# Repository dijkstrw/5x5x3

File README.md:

5x5x3
-----

My third take on a 5x5 macro keyboard, built on top of ZMK / Zephyr. The board
is a custom 5x5 matrix carried by a nice!nano v2 module, with a rotary encoder
on the side and a 25-LED SK6803 strip behind the keys.

What this repo adds on top of stock ZMK lives in `zmk-config/` and is loaded as
an out-of-tree Zephyr module:

- **Per-key light groups**. Each of the 25 LEDs is assigned to a group
  (`DESKTOP`, `VOLUME`, `HID`, `BATTERY`, `LAYER`, `ENDPOINT`, `PROFILE`) via
  the `zmk,light-group` and `zmk,behavior-led-layout` bindings. The group's
  current value indexes into a per-group HSV palette (`zmk,color-group` +
  `zmk,behavior-hsv`), so the LED grid reflects keyboard state at a glance:
  desktop number, volume level, output endpoint, BLE profile, layer, caps/num
  lock, battery, etc.
- **Color effects**. `src/color-effect.c` implements smooth HSV transitions
  for state changes, so values fade rather than snap.
- **`lightgroup` shell command**. A Zephyr shell over USB CDC ACM
  exposing `lightgroup battery|desktop|endpoint|hid|
  layer|profile|volume <value>` allows the host to drive the LED state
  directly. This is needed to update `desktop` and can be used to
  debug the other states.
- **Custom board**. `boards/dijkstra/5x5x3` defines the
  nice!nano-based matrix, the rotary encoder node, and the SK6803 SPI
  LED strip.

Schematic
---------

A kicad schematic and layout for 2 boards lives in `schematic`. The
bottom board carries the nice!nano v2, battery, on/off switch,
blackmagic/arm swd programming port, and breaks out to connections for
the top board. The top board is carries Kailh v2 low profile switches,
sk6803 leds underneath each switch.

Default keymap
--------------

The shipping keymap (`zmk-config/boards/dijkstra/5x5x3/5x5x3.keymap`) is a
small worked example of every custom trait above. Excerpt:

    keymap {
        compatible = "zmk,keymap";
        default_layer {
            bindings = <
                &kp F13       &kp F14       &kp F15       &kp F16       &kp K_MUTE
                &kp F17       &kp F18       &kp F19       &kp F20       &kp F21
                &kp RC(LEFT)  &kp LEFT      &kp K_PP      &kp RIGHT     &kp RC(RIGHT)
                &kp K_APP     &kp C_AL_DOCS &kp C_AL_LOCK &kp C_AL_FILES&kp C_AL_WWW
                &out OUT_TOG  &bt BT_NXT    &kp F22       &kp F23       &kp F24
            >;
            sensor-bindings = <&inc_dec_kp C_VOL_UP C_VOL_DN>;
        };
    };

The bottom-left two keys exercise BLE: `&out OUT_TOG` toggles between USB
and BLE output, `&bt BT_NXT` cycles BLE profile slots. The encoder is wired
through `sensor-bindings` to send `C_VOL_UP` / `C_VOL_DN`.

`ledlayout` maps the physical LED order on the SK6803 strip to the row/col
grid (the strip snakes, so row 1 reverses):

    ledlayout {
        compatible = "zmk,behavior-led-layout";
        bindings = [ 00 01 02 03 04
                     09 08 07 06 05
                     0a 0b 0c 0d 0e
                     13 12 11 10 0f
                     14 15 16 17 18 ];
    };

`lightgroup` assigns each LED to a state-driven group. Here rows 1-2 show the
active desktop, row 3 the volume bar, row 4 caps/num lock + battery, row 5
endpoint / BLE profile / active layer:

    lightgroup {
        compatible = "zmk,light-group";
        default_layer {
            bindings = [ LG_DESKTOP  LG_DESKTOP  LG_DESKTOP  LG_DESKTOP  LG_DESKTOP
                         LG_DESKTOP  LG_DESKTOP  LG_DESKTOP  LG_DESKTOP  LG_DESKTOP
                         LG_VOLUME   LG_VOLUME   LG_VOLUME   LG_VOLUME   LG_VOLUME
                         LG_HID      LG_HID      LG_HID      LG_BATTERY  LG_BATTERY
                         LG_ENDPOINT LG_PROFILE  LG_LAYER    LG_LAYER    LG_LAYER  ];
        };
    };

`colorgroup` provides the HSV palette each group indexes into. For example
battery has five colors representing the 0/25/50/75/100% buckets, desktops
have ten colors for ten desktops, endpoints have three (USB + two BLE):

    colorgroup {
        compatible = "zmk,color-group";
        batterys  { colors = <&hsv HSV_MAGENTA &hsv HSV_RED &hsv HSV_YELLOW &hsv HSV_GREEN &hsv HSV_GREEN>; };
        desktops  { colors = <&hsv HSV_CHARTREUSE &hsv HSV_YELLOW &hsv HSV_ROSE &hsv HSV_VIOLET &hsv HSV_AZURE
                              &hsv HSV_MAGENTA &hsv HSV_VOLTA &hsv HSV_CYAN &hsv HSV_SPRING &hsv HSV_CRIMSON>; };
        endpoints { colors = <&hsv HSV_RED &hsv HSV_GREEN &hsv HSV_BLUE>; };
        ...
    };

Together: ZMK events (layer change, BLE profile change, battery level,
HID caps/num indicator, serial cli update) update each group's value,
the group's current value picks a color from the palette, and the LEDs
assigned to that group on the active layer fade to it.

Building
--------

5x5x3 assumes you have `direnv` and that `.envrc` is automatically
sourced. This will setup a local `.venv` and install `west` using
`uv`.

After that you need `zmk` for keyboard source firmware files, `zephyr`
for the rtos source, which includes an usb and bt stack, and the NRF52
hal, and finally an SDK for cross-compiling to NRF52.

``` shell
make init
```

Retrieves the `zmk` and `zephyr` source, and installs all python
modules we need for building.

If you have not developed with `zephyr` before you also need a Zephyr
SDK. Go to the `zmk` directory and run `west sdk install`.

Note that your source directory will balloon to between 1.5 and almost
5GB due to all the downloaded dependencies.

With all deps loaded;

``` shell
make build
```

Will build a lean production firmware that contains;
- BLE
- USB
- kscan in interrupt mode
- shell with just the lightgroup command.

``` shell
make debug
```

Will build a debug firmwire with:
- more logging
- kernel/gpio/bt/settings shells
- RTT over the SWD probe
- polling kscan

``` shell
make flash
```

Will attempt to flash the resulting firmware to the board via a Black
Magic Probe at `blackmagic.lan:2022`.

``` shell
make serial
```

Will open a terminal to the keyboard's USB CDC ACM, after it has
attached e.g. via USB.

Debugging
---------
Enable debug logging for zmk:

    log enable dbg zmk

Look at zephyr kernel threads and the amount of stack use of each:

    kernel thread list
    kernel thread stacks

Links
-----

- [ZMK](https://github.com/zmkfirmware/zmk): wireless keyboard firmware
- [Zephyr](https://github.com/zephyrproject-rtos/zephyr): RTOS that ZMK is
  built on
- [Black Magic Probe](https://github.com/blackmagic-debug/blackmagic): open
  source SWD/JTAG debug probe firmware used for flashing and RTT

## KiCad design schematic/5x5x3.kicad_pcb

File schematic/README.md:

Third iteration of my 5x5;
- based on zmk, using the nicenano2 board / Supermini RF52840

Questions:
- Can the LDO keep up with 25 sk6803s?

25 * 5mA = 125mA, within range of charger and ldo on nicenano2

- Where are the specific pins for spi / i2c?

RF52840 can reconfigure its pins, so can be assigned to work well with
whatever layout we want.

Other keyboard projects of interest:

- foostan: corne / crkb: the first time I saw sk6812 in mini-e
  variant.

  https://github.com/foostan/kbd
  https://github.com/foostan/crkbd

  MIT license, parts reused:
  - Source of YS-SK6812-MINI-E schematic symbol, and 3d step model.

- Stefan Hamminga: sk6812mini model that models the underside of the
  package best.

- Spamwax: nicenano v2 step model

  https://www.printables.com/model/1181384-nicenano-mcu/files

- Supermini NRF52840 site

  https://wiki.icbbuy.com/doku.php?id=developmentboard:nrf52840

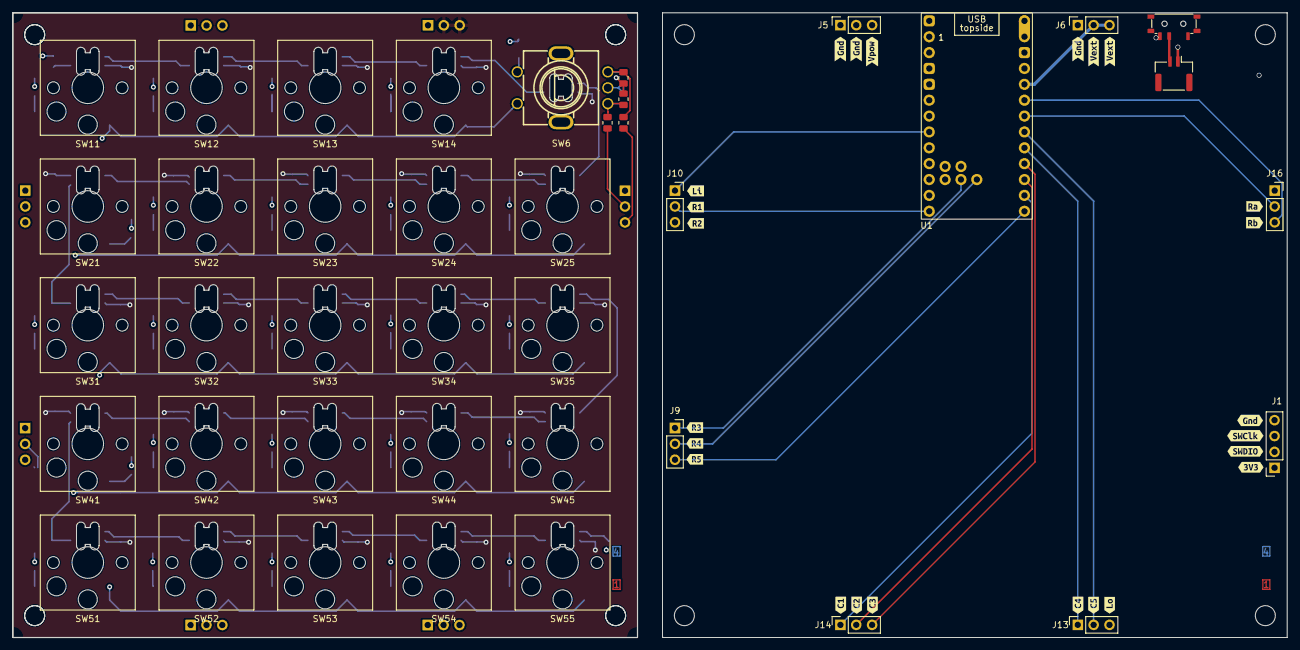
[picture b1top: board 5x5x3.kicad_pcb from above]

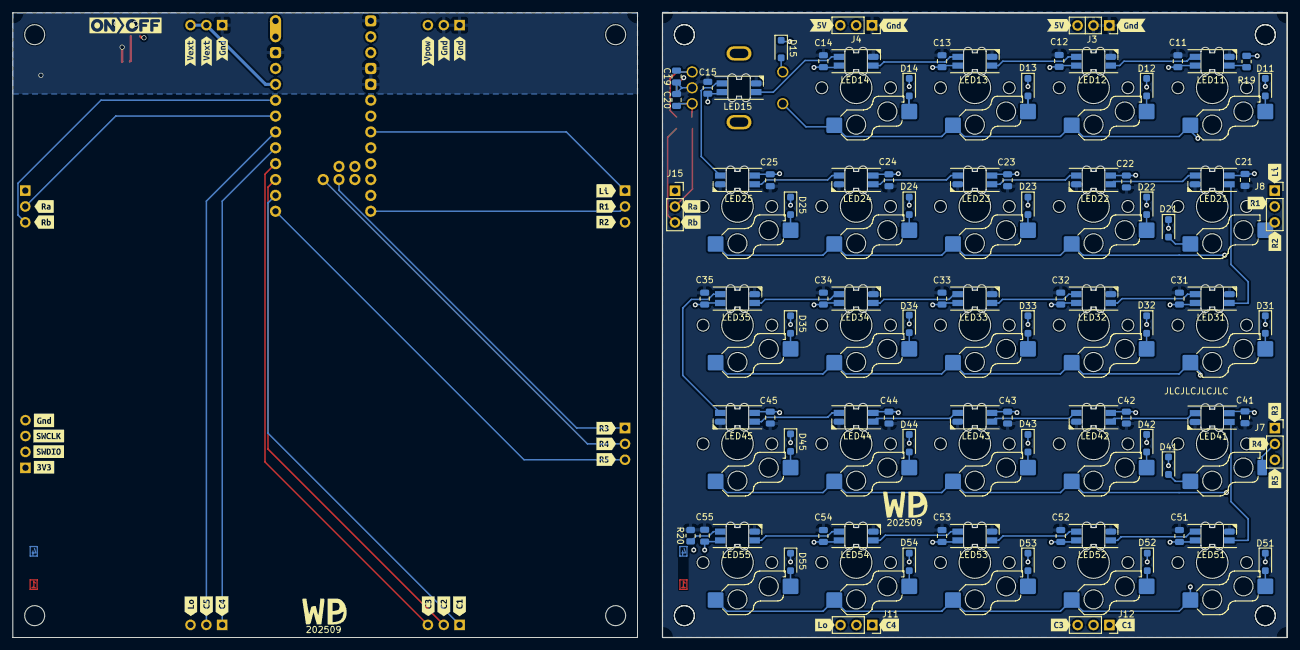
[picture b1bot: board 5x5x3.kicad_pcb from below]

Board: 4 copper layers, 204.0 x 100.0 mm, 192 parts (128 on the bottom side), 72 nets.

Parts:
C11, C12, C13, C14, C15, C19, C20, C21, C22, C23, C24, C25, C31, C32, C33, C34, C35, C41, C42, C43, C44, C45, C51, C52, C53, C54, C55: 100n; C_0805_2012Metric
D11, D12, D13, D14, D15, D21, D22, D23, D24, D25, D31, D32, D33, D34, D35, D41, D42, D43, D44, D45, D51, D52, D53, D54, D55: 1N4148; D_SOD-123F
J1: SW Debug; PinSocket_1x04_P2.54mm_Vertical
J2: Battery; JST_GH_BM02B-GHS-TBT_1x02-1MP_P1.25mm_Vertical
J3, J4, J7, J8, J11, J12, J15: Conn_01x03_Male; PinSocket_1x03_P2.54mm_Vertical
J5, J6, J9, J10, J13, J14, J16: Conn_01x03_Female; PinSocket_1x03_P2.54mm_Vertical
LED11: SK68XXMINI-E; YS-SK6812MINI-E
LED12, LED13, LED14, LED15, LED21, LED22, LED23, LED24, LED25, LED31, LED32, LED33, LED34, LED35, LED41, LED42, LED43, LED44, LED45, LED51, LED52, LED53, LED54, LED55: SK6812MINI-E; YS-SK6812MINI-E
PWSW1: SW_SPST; SW_MSK12C02-HB
R15, R16, R17, R18: 10k; R_0805_2012Metric
R19: 220; R_0805_2012Metric
R20: 470; R_0805_2012Metric
SW6: ALPS_EC11; SW-TH_EC11XXXXXXXX
SW11, SW12, SW13, SW14, SW21, SW22, SW23, SW24, SW25, SW31, SW32, SW33, SW34, SW35, SW41, SW42, SW43, SW44, SW45, SW51, SW52, SW53, SW54, SW55: SW; SW_Hotswap_Kailh_Choc_V1V2_1.00u
U1: nice_nano v2; nice_nano_AH_USBup
kibuzzard-62AF6B0E: G***; kibuzzard-62AF6B0E
kibuzzard-62AF6B7C, kibuzzard-62AF6B7C#2: G***; kibuzzard-62AF6B7C
kibuzzard-62AF6B38, kibuzzard-62AF6B38#2: G***; kibuzzard-62AF6B38
kibuzzard-62AF6BA3, kibuzzard-62AF6BA3#2: G***; kibuzzard-62AF6BA3
kibuzzard-62AF6BAD, kibuzzard-62AF6BAD#2: G***; kibuzzard-62AF6BAD
kibuzzard-62AF6BF3: G***; kibuzzard-62AF6BF3
kibuzzard-62AF6D1E, kibuzzard-62AF6D1E#2: G***; kibuzzard-62AF6D1E
kibuzzard-62AF6DB1, kibuzzard-62AF6DB1#2: G***; kibuzzard-62AF6DB1
kibuzzard-62AF6E15: G***; kibuzzard-62AF6E15
kibuzzard-62AF6E21: G***; kibuzzard-62AF6E21
kibuzzard-62AF6EB6: G***; kibuzzard-62AF6EB6
kibuzzard-62AF6EDD: G***; kibuzzard-62AF6EDD
kibuzzard-62AF6F00: G***; kibuzzard-62AF6F00
kibuzzard-62AF6F11: G***; kibuzzard-62AF6F11
kibuzzard-62AF7A14: G***; kibuzzard-62AF7A14
kibuzzard-62AF7A28: G***; kibuzzard-62AF7A28
kibuzzard-62AF7A49: G***; kibuzzard-62AF7A49
kibuzzard-62AF7A56: G***; kibuzzard-62AF7A56
kibuzzard-62AF7CA9: G***; kibuzzard-62AF7CA9
kibuzzard-62AF7CCF: G***; kibuzzard-62AF7CCF
kibuzzard-62AF74B5: G***; kibuzzard-62AF74B5
kibuzzard-62AF74BF: G***; kibuzzard-62AF74BF
kibuzzard-62AF74C8: G***; kibuzzard-62AF74C8
kibuzzard-62AF749F: G***; kibuzzard-62AF749F
kibuzzard-62AF7487: G***; kibuzzard-62AF7487
kibuzzard-62AF7492: G***; kibuzzard-62AF7492
kibuzzard-62B6DFF3: G***; kibuzzard-62B6DFF3
kibuzzard-62B6E005: G***; kibuzzard-62B6E005
kibuzzard-68B42C08, kibuzzard-68B42C08#2: G***; kibuzzard-68B42C08
kibuzzard-68B471AC: G***; kibuzzard-68B471AC
kibuzzard-68B471BD: G***; kibuzzard-68B471BD
kibuzzard-68B471DE: G***; kibuzzard-68B471DE
kibuzzard-68B471FE: G***; kibuzzard-68B471FE
kibuzzard-68B472A1: G***; kibuzzard-68B472A1
kibuzzard-68B472AB: G***; kibuzzard-68B472AB
kibuzzard-68B4713C, kibuzzard-68B4713C#2, kibuzzard-68B4713C#3, kibuzzard-68B4713C#4, kibuzzard-68B4713C#5, kibuzzard-68B4713C#6: G***; kibuzzard-68B4713C
kibuzzard-68B4715A, kibuzzard-68B4715A#2: G***; kibuzzard-68B4715A
kibuzzard-68B4721A: G***; kibuzzard-68B4721A
kibuzzard-68B4724C: G***; kibuzzard-68B4724C
kibuzzard-68B4727C: G***; kibuzzard-68B4727C
kibuzzard-68B4728F: G***; kibuzzard-68B4728F
kibuzzard-68B4733A: G***; kibuzzard-68B4733A
kibuzzard-68B47169, kibuzzard-68B47169#2: G***; kibuzzard-68B47169
kibuzzard-68B47213: G***; kibuzzard-68B47213
kibuzzard-68B47243: G***; kibuzzard-68B47243
kibuzzard-68B47320: G***; kibuzzard-68B47320
kibuzzard-68B47329: G***; kibuzzard-68B47329
kibuzzard-68B47332: G***; kibuzzard-68B47332
kibuzzard-68B47346: G***; kibuzzard-68B47346
kibuzzard-68B47351: G***; kibuzzard-68B47351
kibuzzard-685E981C: G***; kibuzzard-685E981C
kibuzzard-685E9829: G***; kibuzzard-685E9829

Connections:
BACKLIGHTIN: J8.1, J10.1, R19.2, U1.7 (P0.22)
BACKLIGHTOUT: J11.3, J13.3, LED55.2 (DOUT), R20.1
COL1: D11.1 (K), D21.1 (K), D31.1 (K), D41.1 (K), D51.1 (K), J12.1, J14.1, U1.23 (P0.10-LF)
COL2: D12.1 (K), D22.1 (K), D32.1 (K), D42.1 (K), D52.1 (K), J12.2, J14.2, U1.22 (P1.11-LF)
COL3: D13.1 (K), D23.1 (K), D33.1 (K), D43.1 (K), D53.1 (K), J12.3, J14.3, U1.21 (P1.13-LF)
COL4: D14.1 (K), D24.1 (K), D34.1 (K), D44.1 (K), D54.1 (K), J11.1, J13.1, U1.20 (P1.15-LF)
COL5: D15.1 (K), D25.1 (K), D35.1 (K), D45.1 (K), D55.1 (K), J11.2, J13.2, U1.19 (P0.02-LF)
GND: C11.2, C12.2, C13.2, C14.2, C15.2, C19.2, C20.2, C21.2, C22.2, C23.2, C24.2, C25.2, C31.2, C32.2, C33.2, C34.2, C35.2, C41.2, C42.2, C43.2, C44.2, C45.2, C51.2, C52.2, C53.2, C54.2, C55.2, J1.4, J2.1, J3.1, J3.2, J4.1, J5.1, J5.2, J6.1, LED11.3 (VSS), LED12.3 (VSS), LED13.3 (VSS), LED14.3 (VSS), LED15.3 (VSS), LED21.3 (VSS), LED22.3 (VSS), LED23.3 (VSS), LED24.3 (VSS), LED25.3 (VSS), LED31.3 (VSS), LED32.3 (VSS), LED33.3 (VSS), LED34.3 (VSS), LED35.3 (VSS), LED41.3 (VSS), LED42.3 (VSS), LED43.3 (VSS), LED44.3 (VSS), LED45.3 (VSS), LED51.3 (VSS), LED52.3 (VSS), LED53.3 (VSS), LED54.3 (VSS), LED55.3 (VSS), R20.2, SW6.C, U1.3 (GND), U1.4 (GND), U1.14 (GND), U1.28 (GND)
unnamed: C19.1, R15.2, R16.2, SW6.B
unnamed: C20.1, R17.2, R18.2, SW6.A
unnamed: D11.2 (A), SW11.2
unnamed: D12.2 (A), SW12.2
unnamed: D13.2 (A), SW13.2
unnamed: D14.2 (A), SW14.2
unnamed: D21.2 (A), SW21.1
unnamed: D22.2 (A), SW22.2
unnamed: D23.2 (A), SW23.2
unnamed: D24.2 (A), SW24.2
unnamed: D25.2 (A), SW25.2
unnamed: D31.2 (A), SW31.2
unnamed: D32.2 (A), SW32.2
unnamed: D33.2 (A), SW33.2
unnamed: D34.2 (A), SW34.2
unnamed: D35.2 (A), SW35.2
unnamed: D41.2 (A), SW41.1
unnamed: D42.2 (A), SW42.2
unnamed: D43.2 (A), SW43.2
unnamed: D44.2 (A), SW44.2
unnamed: D45.2 (A), SW45.2
unnamed: D51.2 (A), SW51.2
unnamed: D52.2 (A), SW52.2
unnamed: D53.2 (A), SW53.2
unnamed: D54.2 (A), SW54.2
unnamed: D55.2 (A), SW55.2
unnamed: LED11.4 (DIN), R19.1
unnamed: LED11.2 (DOUT), LED12.4 (DIN)
unnamed: LED12.2 (DOUT), LED13.4 (DIN)
unnamed: LED13.2 (DOUT), LED14.4 (DIN)
unnamed: LED14.2 (DOUT), LED15.4 (DIN)
unnamed: LED15.2 (DOUT), LED25.4 (DIN)
unnamed: LED21.4 (DIN), LED22.2 (DOUT)
unnamed: LED21.2 (DOUT), LED31.4 (DIN)
unnamed: LED22.4 (DIN), LED23.2 (DOUT)
unnamed: LED23.4 (DIN), LED24.2 (DOUT)
unnamed: LED24.4 (DIN), LED25.2 (DOUT)
unnamed: LED31.2 (DOUT), LED32.4 (DIN)
unnamed: LED32.2 (DOUT), LED33.4 (DIN)
unnamed: LED33.2 (DOUT), LED34.4 (DIN)
unnamed: LED34.2 (DOUT), LED35.4 (DIN)
unnamed: LED35.2 (DOUT), LED45.4 (DIN)
unnamed: LED41.4 (DIN), LED42.2 (DOUT)
unnamed: LED41.2 (DOUT), LED51.4 (DIN)
unnamed: LED42.4 (DIN), LED43.2 (DOUT)
unnamed: LED43.4 (DIN), LED44.2 (DOUT)
unnamed: LED44.4 (DIN), LED45.2 (DOUT)
unnamed: LED51.2 (DOUT), LED52.4 (DIN)
unnamed: LED52.2 (DOUT), LED53.4 (DIN)
unnamed: LED53.2 (DOUT), LED54.4 (DIN)
unnamed: LED54.2 (DOUT), LED55.4 (DIN)
ROTA: J15.2, J16.2, R18.1, U1.18 (P0.29-LF)
ROTB: J15.3, J16.3, R15.1, U1.17 (P0.31-LF)
ROTD: J8.2, J10.2, SW6.D, SW11.1, SW12.1, SW13.1, SW14.1, U1.12 (P1.06-LF)
ROTE: D15.2 (A), SW6.E
ROW2: J8.3, J10.3, SW21.2, SW22.1, SW23.1, SW24.1, SW25.1, U1.25 (P1.01-LF)
ROW3: J7.1, J9.1, SW31.1, SW32.1, SW33.1, SW34.1, SW35.1, U1.26 (P1.02-LF)
ROW4: J7.2, J9.2, SW41.2, SW42.1, SW43.1, SW44.1, SW45.1, U1.27 (P1.07-LF)
ROW5: J7.3, J9.3, SW51.1, SW52.1, SW53.1, SW54.1, SW55.1, U1.24 (P0.09-LF)
SWCLK: J1.3, U1.J4 (SWCLK)
SWDIO: J1.2, U1.J3 (SWDIO)
Vbatt: J2.2, PWSW1.2 (B)
Vext: C11.1, C12.1, C13.1, C14.1, C15.1, C21.1, C22.1, C23.1, C24.1, C25.1, C31.1, C32.1, C33.1, C34.1, C35.1, C41.1, C42.1, C43.1, C44.1, C45.1, C51.1, C52.1, C53.1, C54.1, C55.1, J4.2, J4.3, J6.2, J6.3, LED11.1 (VDD), LED12.1 (VDD), LED13.1 (VDD), LED14.1 (VDD), LED15.1 (VDD), LED21.1 (VDD), LED22.1 (VDD), LED23.1 (VDD), LED24.1 (VDD), LED25.1 (VDD), LED31.1 (VDD), LED32.1 (VDD), LED33.1 (VDD), LED34.1 (VDD), LED35.1 (VDD), LED41.1 (VDD), LED42.1 (VDD), LED43.1 (VDD), LED44.1 (VDD), LED45.1 (VDD), LED51.1 (VDD), LED52.1 (VDD), LED53.1 (VDD), LED54.1 (VDD), LED55.1 (VDD), U1.16 (3V3)
Vpowered: J1.1, J3.3, J5.3, PWSW1.3 (C), R16.1, R17.1, U1.13 (BAT+), U1.29 (BAT+)

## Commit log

2024-09-06 Started with new zmk choc 5x5
2024-09-08 Moving to zmk-config board config
2024-09-14 First valid configuration
    Lacks a lot of things, but does allow me to validate the 5x5 layout
    and pin reassignments.
2024-09-14 Added zmk as submodule inside the repo
2025-01-26 add ledstrip via spi
    - spi0 at the arduino micro side ends up on p0.10 in nice nano
    land. This pin is lf, and might interfere with the antenna according
    to nordic.
    - spi0 has a hardware issue that requires an enabled sck pin on the
    nrf52840. Moving to spi3 because that does not have that issue.
    - make sure to set status to okay to enable driver...
2025-01-31 Added shell with custom prompt
    Removed all shell modules not required.
2025-02-09 Remove warning
2025-02-09 Add HSV color configuration in keymap
    First steps towards a custom driver that has the notion of lightgroups
    to show what the status according to the keyboard is.
2025-02-16 WIP: all broken, but let it simmer for a while
2025-02-22 Device configuration is entered, but storage definitions are off
    So we have a start!
2025-02-28 Updated device configuration
    Learned a couple of dts attributes:
    - all items have to have a definition of how big they are
    - inside zmk this is handled by specifying for leaf behaviors how many
    #binding-cells they are
    - which also explains the use and overloading of the word binding
2025-02-28 Retrieve dts in c
2025-03-01 Add clangd, start looking at using dt from c
2025-03-30 First light on light-group implementation
    - dts is parsed and configured, but not used yet
    - our own timer and worker are called
    Still, after much horsing about -- success!
2025-04-06 First apply according to light groups
    Note that each light group shows you a status for something, and
    that something as an input (e.g. current volume, current hid,
    current endpoint) are missing.
2025-04-09 First light with light groups
2025-04-09 Work out continuous range arithmetic
2025-04-12 Remove UF2 output format
    Development cycle is faster to flash via blackmagic
2025-04-12 Add shell commands
2025-04-13 Fix hsv transition: hue movement now correct
2025-04-13 Adjust speed: transition in 1 second
2025-04-17 Rewrite similar devicetree color ranges into one statement
    This shows much clearer what we pull out of device tree than the
    previous wall of text, where the crucial bits were scattered over
    the page.
2025-04-17 Fix call signature of the light_group_range/continuous functions
    I tried to follow clang error logging in my fixes before but thought
    at the end it looked really ugly. Now after some sleep the error in my
    ways is clear.
2025-04-17 Respond to zmk events by reacting with light groups
2025-04-18 Add battery event handling
2025-04-18 Fix pixel effect init call arguments
    Initially I wanted to keep the arguments to the different
    pixel_effect_* functions the same, but that makes no sense if they are
    doing something different and have different starting requirements.
2025-04-18 Add light group actions for background
2025-04-18 Fix event handlers and document their argument meanings
2025-04-19 Deal with power: state at on/usb powered/ble/idle
    The defaults:
    - on start: on
    - on usb powered: on
    - on idle: off
    - on usb no power: off
    Also clean up taking arguments from the shell. Adjustment to max group
2025-04-20 Simplify power control logic
    The previous power management was overly complex and unintuitive. Disabling external power persisted even when USB power was available and the device was idle, leading to confusion (e.g., no lights d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
    This commit simplifies the logic:
    - USB power: Lights on.
    - Idle: Lights off.
    - USB power loss: Lights off.
2025-04-20 First stab at a serial connector using rust
2025-04-26 Rewrite to susanoo to c
    I found the rust way to complex and busy with rust specific problems
    that obscured the problem that I'm trying to solve.
    This is a simple c approach; again, the python version is more
    powerful, somewhat similar in complexity to read, so going to mull
    over this some more.
2025-04-26 Remove the rust approach
2025-04-26 Add shell commands for everything, and cleanup code
    Added shell commands for all light groups, even though most internal
    things are not really needed there. With this serial experimentation
    becomes easier.
    The code is now organised in sections, with a little explanation of
    what is going to happen next.
2025-04-27 Fix BLE-less compilation
    BLE has real-world timing constraints and will break if we lose track
    of time because we are horsing about in the debugger.
    BLE-less builds can be debugged at will.
2025-04-28 Fixed continuous range calculations
    It took some time for me to understand that the spaces between
    successive colors are the buckets. So the original code had a off by
    one error.
    Also improved the battery color shading to my eye. Battery group will
    stay green from roughly 60% to 100% and change to worrying shades
    (first red, then when it is really important that you seek external
2025-04-28 Map battery percentages to frac8_t
    We get battery in terms of percentages, but calculate fractions
    internally using frac8_t. frac8_t is a percentage expressed in 0-255,
    instead of 0-100. So whenever we get a battery input (event or serial)
    convert to the internal representation.
2025-05-18 Started with layout
2025-06-22 Connect up the keys, rough placing of components
    Need to find a good switch, and maybe rearrange the row / col pins to
    better align with 5x5 layout.
    Currently targetting 4 layer board
2025-06-27 Adjusted powerswitch, battery terminal, rotary encoder
2025-07-06 Routed rows and columns
2025-08-15 Leds now connected to right pin 0.22
2025-08-29 Back to 100x100; aim for 5x5x2 hw compat now
    After dithering a long time I am going back to 100x100;
    1. 5x5x3 keyboard can then be used on a 5x5x2 carrier, and vice versa.
    2. I2C oled screen does not fit nicely in the room I had
    3. zmk support for both rgb and i2c powercontrol is in
    development (and has been for some time)
    4. With expressive leds, who needs another screen
2025-08-29 Mapped 5x5x2 pins onto 5x5x3
    But there is overlap, so some work is needed. Also, what rubbish am I
    bringing in from the old file?
2025-08-30 Routed cols and rows
2025-08-31 Keyboard routed, added kibuzzard labels on mcu board
2025-09-15 Adjusted layer indications, component label legibility, routed mcu
2025-10-12 Add mcu board logos
2025-10-12 Add logos, cleanup routes, cleanup legends
2025-10-12 Applied DRC
2025-10-12 As ordered 20251012 at JLCPCB
    Note that the board file was saved twice and cut up to be sent as
    separate gerbers.
2026-05-15 Bug: memset arguments were wrong way around
2026-05-15 Moved to latest zmk
    - zmk at v0.3-123-gead91ca0, zephyr now at 4.1.0
    - zmk now requires HMWv2 layout:
    - New boards/dijkstra/5x5x3/board.yml declaring name/vendor/soc.
    - zmk-config/boards/arm/5x5x3/ → zmk-config/boards/dijkstra/5x5x3/
    - Kconfig.board → Kconfig.5x5x3 with config BOARD_5X5X3 /
    select SOC_NRF52840_QIAA.
2026-05-15 Adjusted to pins as on the 5x5x3 board
2026-05-15 Add shell and logging to be able to debug
2026-05-16 Add and enable rotary encoder
2026-05-16 Separate debug out, enable ble and test further
2026-05-17 Add Makefile with example targets
2026-05-17 Enable serial always for access to lightgroup cmd
2026-05-17 Cleanup gitignore
    Buy ignoring `zmk` I'm ignoring critical color include files - doh!
2026-05-17 Add color and lightgroup definitions
2026-05-17 Add pictures to README.md
2026-05-17 Add a clean target
2026-05-17 Adjust schematic to 5x5x3
2026-05-17 Make .envrc install python and west if needed
2026-05-17 Adjust Makefile and README.md for better first time experience
2026-05-17 Debugged bluetooth pairing
    There is now a dedicated layer for bluetooth profile management,
    clearing and pin code entering.
    Also: when a layer is changed, all led groups need updating.
2026-05-17 Ensure we have logging on debug build
2026-05-17 Add links to README.md
2026-05-17 README.md formatting
